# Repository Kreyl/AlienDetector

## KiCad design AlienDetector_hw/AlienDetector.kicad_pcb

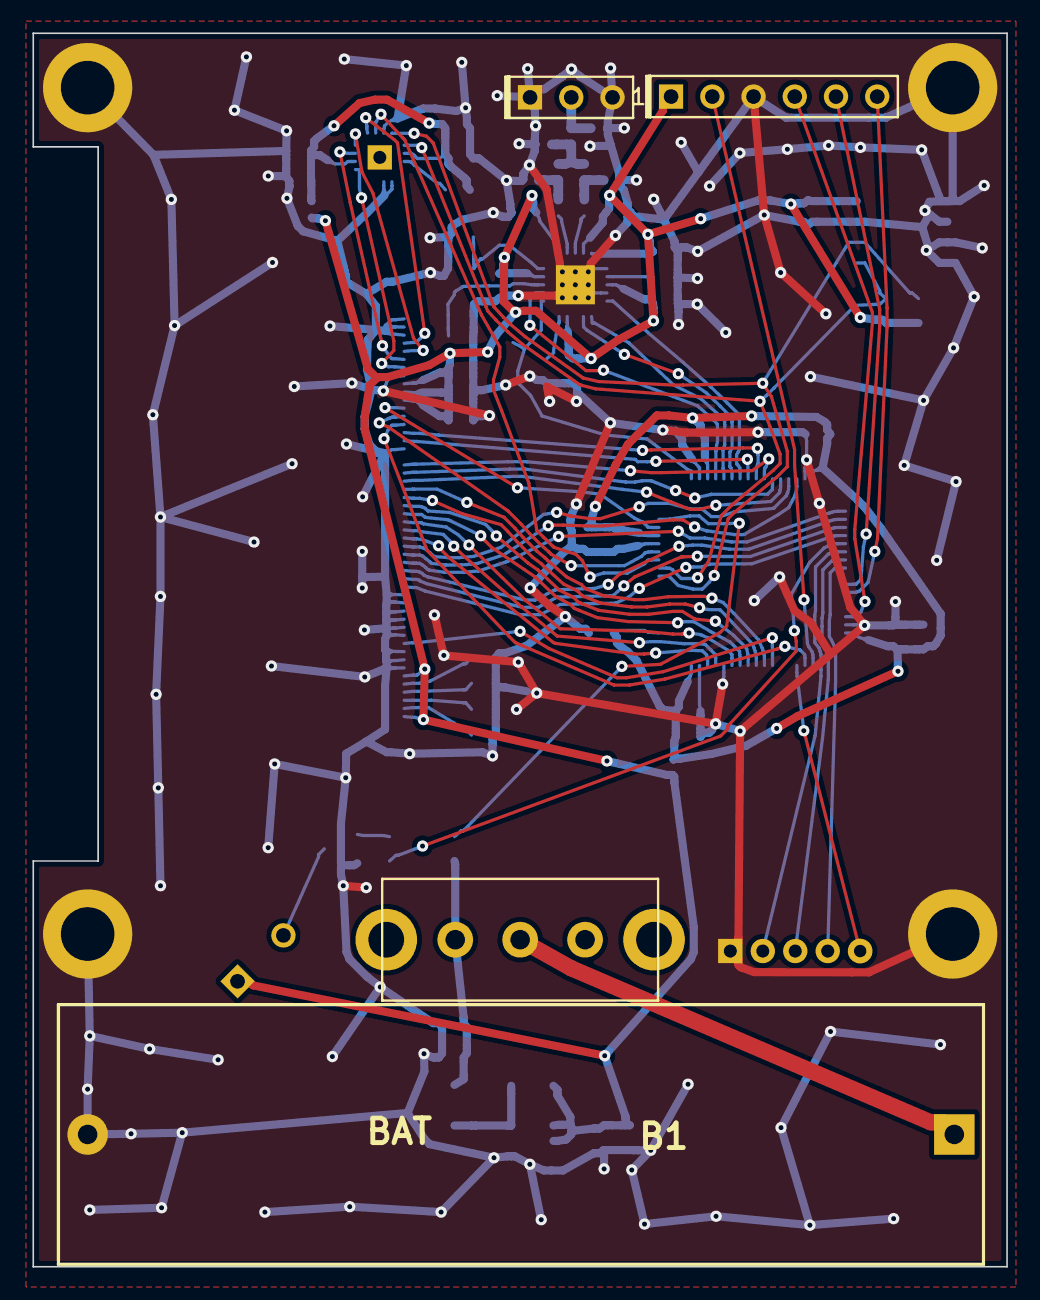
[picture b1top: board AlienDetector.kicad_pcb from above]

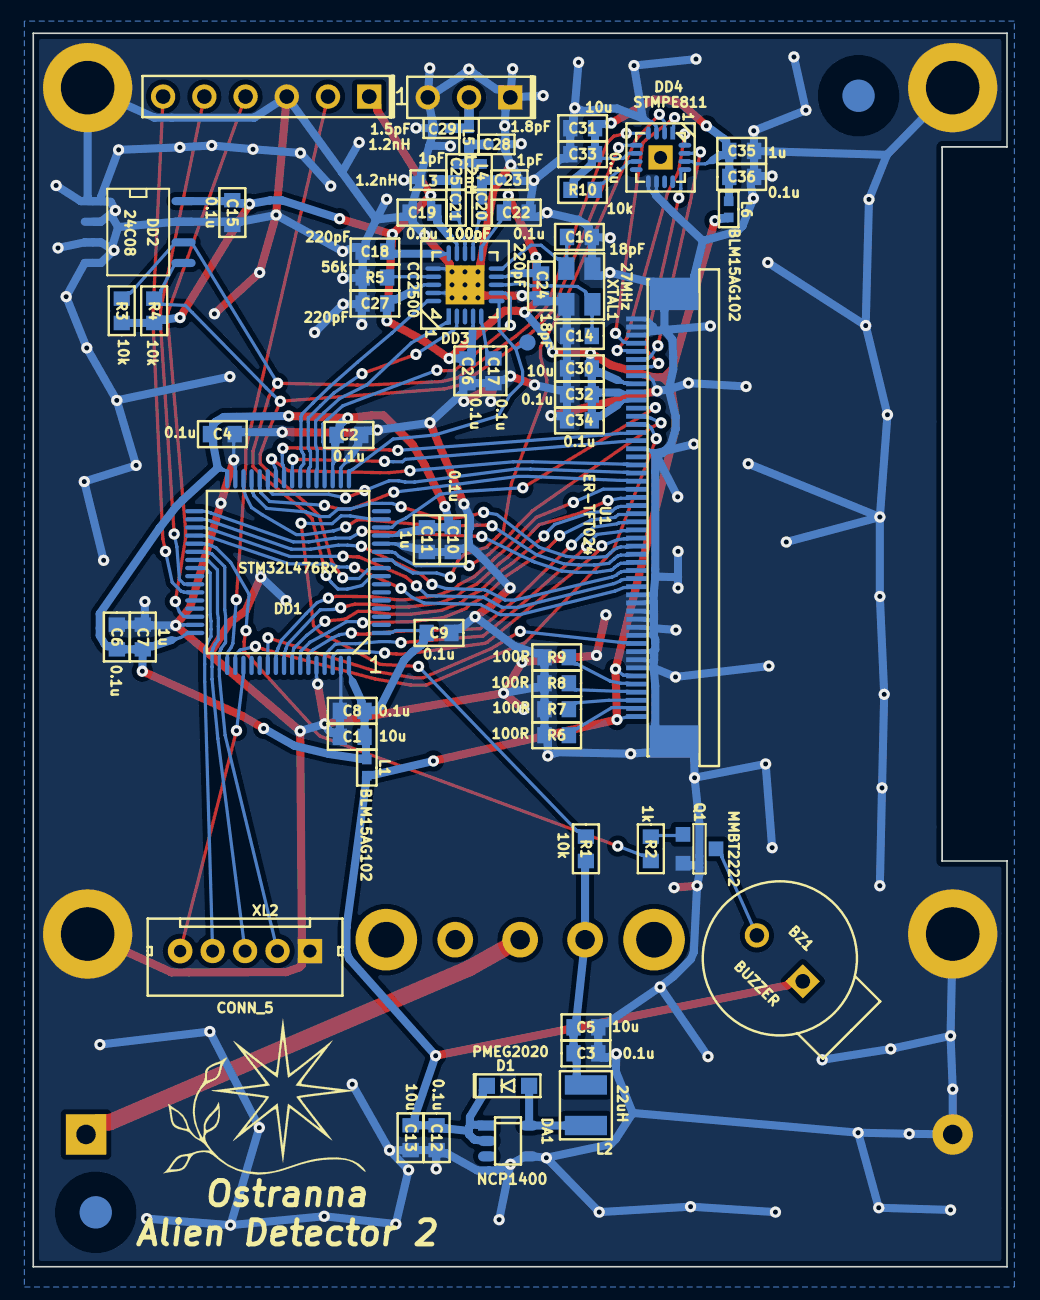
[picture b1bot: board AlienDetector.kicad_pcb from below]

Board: 2 copper layers, 60.0 x 76.0 mm, 75 parts (67 on the bottom side), 68 nets.

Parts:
B1: BAT; BATTERY_AA
BZ1: BUZZER; BUZZER_HC0903
C1, C5, C13, C30, C31: 10u; CAP_0603
C2, C3, C4, C6, C8, C9, C10, C12, C15, C17, C19, C22, C26, C32, C33, C34, C36: 0.1u; CAP_0603
C7, C11, C35: 1u; CAP_0603
C14, C16: 18pF; CAP_0603
C18, C24, C27: 220pF; CAP_0603
C20, C21: 100pF; CAP_0402
C23, C25: 1pF; CAP_0402
C28: 1.8pF; CAP_0402
C29: 1.5pF; CAP_0402
D1: PMEG2020; SOD323
DA1: NCP1400; SOT23-5
DD1: STM32L476Rx; LQFP64
DD2: 24C08; SO8_150MIL
DD3: CC2500; QFN20
DD4: STMPE811; QFN16_4x4_H
HOLE1, HOLE2, HOLE3, HOLE4: HOLE_METALLED; Hole3d3_out5d5mm
L1, L6: BLM15AG102; IND_0402
L2: 22uH; IND_1210_LQH32C
L3, L4, L5: 1.2nH; IND_0402
Logo1: Logo; Ostranna_12d7_10d1
Q1: MMBT2222; SOT23-3
R1, R3, R4, R10: 10k; RES_0603
R2: 1k; RES_0603
R5: 56k; RES_0603
R6, R7, R8, R9: 100R; RES_0603
RP1, RP2: REFPOINT; REF_POINT_2MM
SW1: SWITCH_H; SW_SS9
TP1: TESTPOINT; TESTPOINT_1MM
U1: ER-TFT024; ER-CON50HT-1
XL1: CONN_6; PLS-6
XL2: CONN_5; WB-05(MW-5M)
XL3: CONN_3; PLS-3
XTAL1: 27MHz; 03225C4

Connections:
+3.3V: BZ1.1, C12.1, C13.1, C15.2, C18.1, C19.1, C22.1, C24.1, C26.1, C27.1, C30.1, C32.1, C34.1, D1.C, DA1.1, DA1.2, DD2.8, DD3.4, DD3.9, DD3.11, DD3.14, DD3.15, DD3.18, L1.2, L6.2, R3.1, R4.2, U1.1, U1.6, U1.40, U1.41, U1.42, XL1.1
/A1: C20.1, DD3.12
/A2: C21.1, DD3.13
/A3: C20.2, C23.2, L4.2
/A4: C21.2, C25.1, L3.1
/A5: C25.2, C28.1, L4.1, L5.2
/ADC_BAT: DD1.15, R1.1
/Buzzer: DD1.37, R2.2
/CC_CS: DD1.20, DD3.7
/CC_GDO0: DD1.17, DD3.6, TP1.1
/CC_MISO: DD1.22, DD3.2
/CC_MOSI: DD1.23, DD3.20
/CC_SCK: DD1.21, DD3.1
/LCD_CSX: DD1.11, U1.38
/LCD_D0: DD1.26, U1.32
/LCD_D1: DD1.27, U1.31
/LCD_D2: DD1.28, U1.30
/LCD_D3: DD1.55, U1.29
/LCD_D4: DD1.56, U1.28
/LCD_D5: DD1.57, U1.27
/LCD_D6: DD1.58, U1.26
/LCD_D7: DD1.59, U1.25
/LCD_D8: DD1.61, U1.24
/LCD_D9: DD1.62, U1.23
/LCD_D10: DD1.29, U1.22
/LCD_D11: DD1.30, U1.21
/LCD_D12: DD1.33, U1.20
/LCD_D13: DD1.34, U1.19
/LCD_D14: DD1.35, U1.18
/LCD_D15: DD1.36, U1.17
/LCD_DC: DD1.50, U1.37
/LCD_RD: DD1.24, U1.35
/LCD_RST: DD1.54, U1.10
/LCD_TE: DD1.14, U1.39
/LCD_WR: DD1.25, U1.36
/LCD_X+: DD4.13, U1.44
/LCD_X-: DD4.16, U1.46
/LCD_Y+: DD4.15, U1.45
/LCD_Y-: DD4.1, U1.47
/Lout: D1.A, DA1.5, L2.1
/RF_Out: C29.1, L5.1, XL3.2
/SCL: DD1.8, DD2.6, DD4.4, R3.2
/SDA: DD1.9, DD2.5, DD4.5, R4.1
/SWCLK: DD1.49, XL1.2
/SWDIO: DD1.46, XL1.4
/TOUCH_INT: DD1.10, DD4.2
/TOUCH_PWR: C31.1, C33.1, C35.1, C36.1, DD4.6, DD4.14, L6.1, R10.2
/UART_RX: DD1.43, XL1.6
/UART_TX: DD1.42, XL1.5
GND: B1.C, C1.1, C2.1, C3.2, C4.1, C5.2, C6.1, C7.1, C8.1, C9.1, C10.1, C11.1, C12.2, C13.2, C14.2, C15.1, C16.2, C17.2, C18.2, C19.2, C22.2, C23.1, C24.2, C26.2, C27.2, C28.2, C29.2, C30.2, C31.2, C32.2, C33.2, C34.2, C35.2, C36.2, DA1.4, DD1.12, DD1.18, DD1.31, DD1.47, DD1.60, DD1.63, DD2.1, DD2.2, DD2.3, DD2.4, DD2.7, DD3.16, DD3.19, DD3.PAD, DD4.3, DD4.9, DD4.10, HOLE1.H, HOLE2.H, HOLE3.H, HOLE4.H, L3.2, Q1.2, R5.2, R6.2, R7.2, R8.2, R9.2, U1.7, U1.8, U1.9, U1.11, U1.12, U1.13, U1.14, U1.15, U1.16, U1.34, U1.43, U1.48, U1.49, U1.50, U1.H, XL1.3, XL2.1, XL3.1, XL3.3, XTAL1.H
unnamed: B1.A, SW1.2
unnamed: BZ1.2, Q1.3
unnamed: C3.1, C5.1, L2.2, R1.2, SW1.1
unnamed: C14.1, DD3.8, XTAL1.1
unnamed: C16.1, DD3.10, XTAL1.2
unnamed: C17.1, DD3.5
unnamed: DD1.38, XL2.2
unnamed: DD1.39, XL2.3
unnamed: DD1.40, XL2.4
unnamed: DD1.51, XL2.5
unnamed: DD3.17, R5.1
unnamed: DD4.7, R10.1
unnamed: Q1.1, R2.1
unnamed: R6.1, U1.2
unnamed: R7.1, U1.3
unnamed: R8.1, U1.4
unnamed: R9.1, U1.5
PwrMCU: C1.2, C2.2, C4.2, C6.2, C7.2, C8.2, C9.2, C10.2, C11.2, DD1.1, DD1.13, DD1.19, DD1.32, DD1.48, DD1.64, L1.1

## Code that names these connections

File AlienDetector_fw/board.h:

/*
 * board.h
 *
 *  Created on: 12 ñåíò. 2015 ã.
 *      Author: Kreyl
 */

#pragma once

#include <inttypes.h>

// ==== General ====
#define APP_NAME            "AlienDetector2"

// MCU type as defined in the ST header.
#define STM32L476xx

// Freq of external crystal if any. Leave it here even if not used.
#define CRYSTAL_FREQ_HZ         12000000

// OS timer settings
#define STM32_ST_IRQ_PRIORITY   2
#define STM32_ST_USE_TIMER      5
#define SYS_TIM_CLK             (Clk.APB1FreqHz)    // Timer 5 is clocked by APB1

//  Periphery
#define I2C1_ENABLED            FALSE
#define I2C2_ENABLED            FALSE
#define I2C3_ENABLED            TRUE
#define SIMPLESENSORS_ENABLED   FALSE
#define BUTTONS_ENABLED         FALSE

#define ADC_REQUIRED            FALSE
#define STM32_DMA_REQUIRED      TRUE    // Leave this macro name for OS

// LCD
#define LCD_W           320 // }
#define LCD_H           240 // } Pixels count

#if 1 // ========================== GPIO =======================================
// EXTI
#define INDIVIDUAL_EXTI_IRQ_REQUIRED    FALSE

// Buttons
#define BTN1_PIN        GPIOA, 0, pudNone
#define BTN2_PIN        GPIOC, 13, pudPullUp

// UART
#define UART_GPIO       GPIOA
#define UART_TX_PIN     9
#define UART_RX_PIN     10

// Beeper
#define BEEPER_TOP      22
#define BEEPER_PIN      { GPIOC, 6, TIM3, 1, invNotInverted, omPushPull, BEEPER_TOP }

// LCD
#define LCD_DATA_GPIO   GPIOB
#define LCD_RESET_PIN   GPIOD, 2
#define LCD_CSX_PIN     GPIOC, 3
#define LCD_DC_PIN      GPIOA, 15
#define LCD_WR_PIN      GPIOC, 5
#define LCD_RD_PIN      GPIOC, 4
#define LCD_TE_PIN      GPIOA, 0

// Radio: SPI, PGpio, Sck, Miso, Mosi, Cs, Gdo0
#define CC_Setup0       SPI1, GPIOA, 5,6,7, 4, 3

// I2C
#define I2C1_GPIO       GPIOB
#define I2C1_SCL        6
#define I2C1_SDA        7
#define I2C2_GPIO       GPIOB
#define I2C2_SCL        10
#define I2C2_SDA        11
#define I2C3_GPIO       GPIOC
#define I2C3_SCL        0
#define I2C3_SDA        1
// I2C Alternate Function
#define I2C_AF          AF4

#endif // GPIO

#if 1 // =========================== SPI =======================================
#define CC_SPI          SPI1
#define CC_SPI_AF       AF5
#endif

#if 1 // ========================== USART ======================================
#define PRINTF_FLOAT_EN FALSE
#define CMD_UART        USART1
#define UART_USE_INDEPENDENT_CLK    TRUE
#define UART_TXBUF_SZ   2048
#endif

#if 1 // =========================== I2C =======================================
// i2cclkPCLK1, i2cclkSYSCLK, i2cclkHSI
#define I2C_CLK_SRC     i2cclkHSI
#define I2C_BAUDRATE_HZ 400000
#endif

#if ADC_REQUIRED // ======================= Inner ADC ==========================
// Clock divider: clock is generated from the APB2
#define ADC_CLK_DIVIDER		adcDiv2

// ADC channels
#define ADC_BATTERY_CHNL 	14
// ADC_VREFINT_CHNL
#define ADC_CHANNELS        { ADC_BATTERY_CHNL, ADC_VREFINT_CHNL }
#define ADC_CHANNEL_CNT     2   // Do not use countof(AdcChannels) as preprocessor does not know what is countof => cannot check
#define ADC_SAMPLE_TIME     ast24d5Cycles
#define ADC_OVERSAMPLING_RATIO  64   // 1 (no oversampling), 2, 4, 8, 16, 32, 64, 128, 256
#endif

#if 1 // =========================== DMA =======================================
// ==== Uart ====
// Remap is made automatically if required
#define UART_DMA_TX     STM32_DMA2_STREAM6
#define UART_DMA_RX     STM32_DMA2_STREAM7
#define UART_DMA_CHNL   2

// ==== I2C ====
#define I2C1_DMA_TX     STM32_DMA1_STREAM6
#define I2C1_DMA_RX     STM32_DMA1_STREAM7
#define I2C1_DMA_CHNL   3
#define I2C2_DMA_TX     STM32_DMA1_STREAM4
#define I2C2_DMA_RX     STM32_DMA1_STREAM5
#define I2C2_DMA_CHNL   3
#define I2C3_DMA_TX     STM32_DMA1_STREAM2
#define I2C3_DMA_RX     STM32_DMA1_STREAM3
#define I2C3_DMA_CHNL   3

#if ADC_REQUIRED
#define ADC_DMA         STM32_DMA1_STREAM1
#define ADC_DMA_MODE    STM32_DMA_CR_CHSEL(0) |   /* DMA1 Stream1 Channel0 */ \
                        DMA_PRIORITY_LOW | \
                        STM32_DMA_CR_MSIZE_HWORD | \
                        STM32_DMA_CR_PSIZE_HWORD | \
                        STM32_DMA_CR_MINC |       /* Memory pointer increase */ \
                        STM32_DMA_CR_DIR_P2M |    /* Direction is peripheral to memory */ \
                        STM32_DMA_CR_TCIE         /* Enable Transmission Complete IRQ */
#endif // ADC

#endif // DMA

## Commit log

2018-01-30 Old detector
2018-01-30 Proceeding with PCB
2018-01-30 Proceeding with layout
2018-03-26 v2 layout done
2018-03-26 Proceeding
2018-03-27 PCB sent to factory
2018-04-03 + First steps of FW
2018-04-03 +Column series
2018-04-04 + CC init ok + EE load/save ID
2018-04-05 Random test output
2018-04-05 Seems displaying smoothlly
2018-04-08 Displaying columns
2018-04-09 + beeper
2018-04-09 * Sch changed: beeper switched from 3v3 to 1v5 * Average of received RSSI RC
